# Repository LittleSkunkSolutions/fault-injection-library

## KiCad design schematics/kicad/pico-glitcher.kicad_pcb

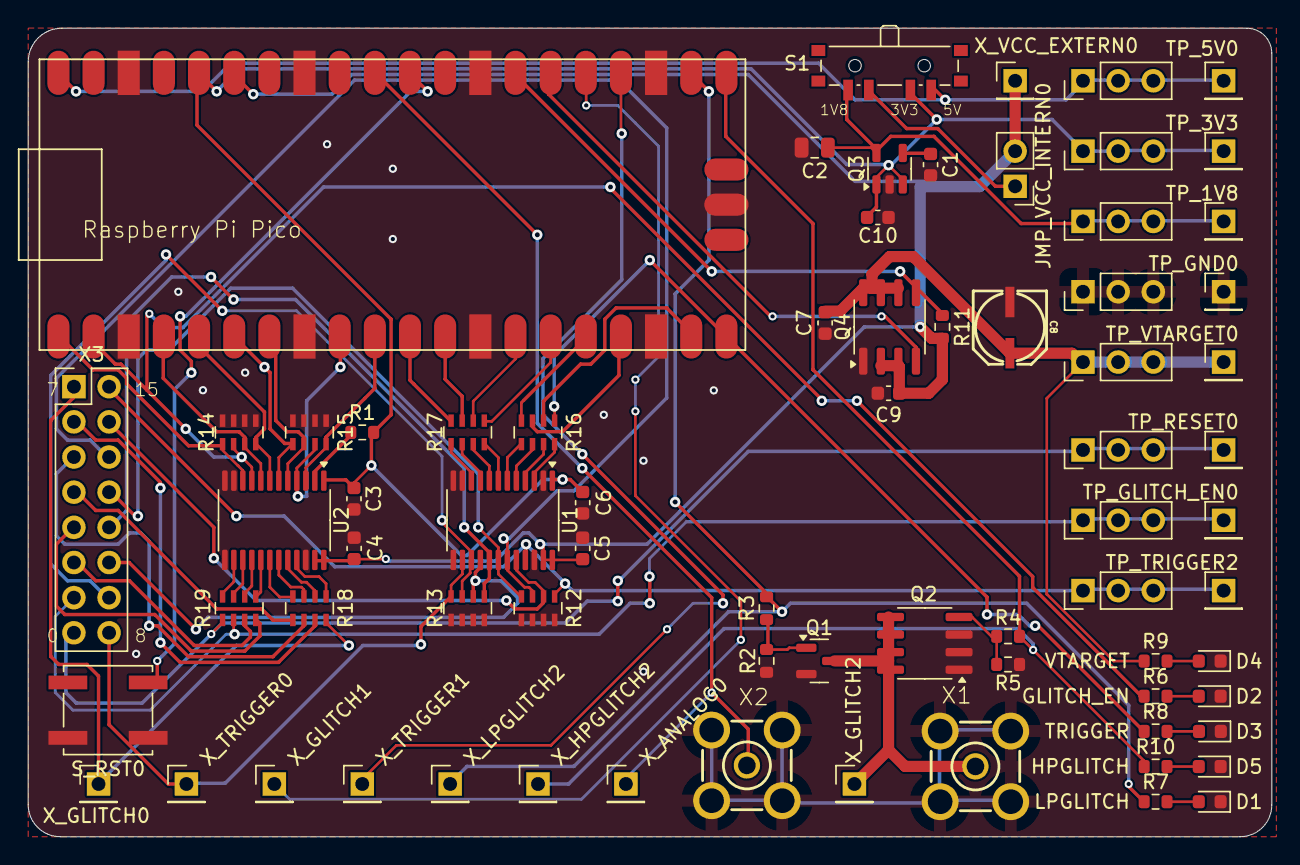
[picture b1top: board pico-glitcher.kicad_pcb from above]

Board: 2 copper layers, 89.8 x 58.4 mm, 72 parts (0 on the bottom side), 73 nets.

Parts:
C1: 10nF; C_0603_1608Metric
C2: 2.2u; C_0805_2012Metric
C3, C4, C5, C6, C7, C9, C10: 0.1uF; C_0603_1608Metric
C8: 22uF; PANASONIC_C
D1: LED_RED_LPGLITCH; LED_0603_1608Metric
D2: LED_BLUE_GLITCH_EN; LED_0603_1608Metric
D3: LED_BLUE_TRIGGER2; LED_0603_1608Metric
D4: LED_RED_TARGET_POWER; LED_0603_1608Metric
D5: LED_RED_HPGLITCH; LED_0603_1608Metric
JMP_VCC_INTERN0: JMP_VCC_INTERN; PinHeader_1x02_P2.54mm_Vertical
PICO0: Raspberry Pi; RPI_PICO
Q1: IRLML2502; SOT-23
Q2: IRF7807PBF; SOIC-8_3.9x4.9mm_P1.27mm
Q3: TPS 79318; SOT-23-5
Q4: TPS2041; SOIC-8_3.9x4.9mm_P1.27mm
R1, R2, R5, R11: 10K; R_0603_1608Metric
R3, R4: 1R; R_0603_1608Metric
R6, R7, R8, R10: 150; R_0603_1608Metric
R9: 220; R_0603_1608Metric
R12, R13, R14, R15: 10k; R_Array_Concave_4x0603
R16, R17, R18, R19: 100; R_Array_Concave_4x0603
S1: Micro Slide Switch; SW_SP3T_PCM13
S_RST0: SW_Push_Shielded; SW_Push_1P1T_NO_CK_KSC7xxJ
TP_1V8, TP_3V3: PINHDR_1X1; PinHeader_1x01_P2.54mm_Vertical
TP_5V0: M01PTH; PinHeader_1x01_P2.54mm_Vertical
TP_GLITCH_EN0: PINHDR_1X1; PinHeader_1x01_P2.54mm_Vertical
TP_GND0: PINHDR_1X1; PinHeader_1x01_P2.54mm_Vertical
TP_RESET0: PINHDR_1X1; PinHeader_1x01_P2.54mm_Vertical
TP_TRIGGER2: PINHDR_1X1; PinHeader_1x01_P2.54mm_Vertical
TP_VTARGET0: PINHDR_1X1; PinHeader_1x01_P2.54mm_Vertical
U1, U2: NH245; TSSOP-24_4.4x7.8mm_P0.65mm
X1, X2: BU-SMA
X3: M08X2; PinHeader_2x08_P2.54mm_Vertical
X_1V8, X_3V3, X_5V0: PINHDR_3X1; PinHeader_1x03_P2.54mm_Vertical
X_ANALOG0: PINHDR_1X1; PinHeader_1x01_P2.54mm_Vertical
X_GLITCH0, X_GLITCH1, X_GLITCH2: PINHDR_1X1; PinHeader_1x01_P2.54mm_Vertical
X_GLITCH_EN0: PINHDR_3X1; PinHeader_1x03_P2.54mm_Vertical
X_GND0: PINHDR_3X1; PinHeader_1x03_P2.54mm_Vertical
X_HPGLITCH2: PINHDR_1X1; PinHeader_1x01_P2.54mm_Vertical
X_LPGLITCH2: PINHDR_1X1; PinHeader_1x01_P2.54mm_Vertical
X_RESET0: PINHDR_3X1; PinHeader_1x03_P2.54mm_Vertical
X_TRIGGER0, X_TRIGGER1: PINHDR_1X1; PinHeader_1x01_P2.54mm_Vertical
X_TRIGGER2: PINHDR_3X1; PinHeader_1x03_P2.54mm_Vertical
X_VCC_EXTERN0: PINHDR_1X1; PinHeader_1x01_P2.54mm_Vertical
X_VTARGET0: PINHDR_3X1; PinHeader_1x03_P2.54mm_Vertical

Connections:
+3V3: C3.1, C6.1, C10.1, PICO0.3V3, Q3.1 (IN), Q3.3 (/EN), R1.2, S1.2, TP_3V3.1, U1.1 (VCCA), U2.1 (VCCA), X_3V3.1, X_3V3.2, X_3V3.3
+5V: PICO0.VBUS, S1.1, TP_5V0.1, X_5V0.1, X_5V0.2, X_5V0.3
/+1V8: C2.1, Q3.5 (OUT), S1.4, TP_1V8.1, X_1V8.1, X_1V8.2, X_1V8.3
/ANALOG: PICO0.GP26_A0, X2.1, X_ANALOG0.1
/GP0: PICO0.GP0, R14.5, U2.10 (A8)
/GP1: PICO0.GP1, R6.1, R14.6, U2.9 (A7)
/GP2: PICO0.GP2, R14.7, U2.8 (A6)
/GP3: PICO0.GP3, R14.8, U2.7 (A5)
/GP4: PICO0.GP4, R15.5, U2.6 (A4)
/GP5: PICO0.GP5, R15.6, U2.5 (A3)
/GP6: PICO0.GP6, R15.7, U2.4 (A2)
/GP7: PICO0.GP7, R15.8, U2.3 (A1)
/GP8: PICO0.GP8, R17.4
/GP9: PICO0.GP9, R17.3
/GP10: PICO0.GP10, R17.2
/GP11: PICO0.GP11, R17.1
/GP12: PICO0.GP12, R16.4
/GP13: PICO0.GP13, R16.3
/GP14: PICO0.GP14, R16.2
/GP15: PICO0.GP15, R8.1, R16.1
/HPGLITCH2: PICO0.GP16, R4.1, R10.1, X_HPGLITCH2.1
/JVCC: JMP_VCC_INTERN0.1, S1.3
/LPGLITCH2: PICO0.GP17, R3.2, R7.1, X_LPGLITCH2.1
/VTARGET: C7.1, C8.1, Q4.6 (OUT), Q4.7 (OUT), Q4.8 (OUT), R9.1, TP_VTARGET0.1, X_VTARGET0.1, X_VTARGET0.2, X_VTARGET0.3
/VTARGET_EN: PICO0.GP20, Q4.4 (/EN)
/VTARGET_OC: PICO0.GP21, Q4.5 (/OC), R11.1
GND: C1.2, C2.2, C3.2, C4.1, C5.1, C6.2, C7.2, C8.2, C9.1, C10.2, D1.1 (K), D2.1 (K), D3.1 (K), D4.1 (K), D5.1 (K), PICO0.AGND, PICO0.GND@1 (GND), PICO0.GND@2 (GND), PICO0.GND@3 (GND), PICO0.GND@4 (GND), PICO0.GND@5 (GND), PICO0.GND@6 (GND), PICO0.GND@7 (GND), PICO0.GND@8 (GND), Q1.2 (S), Q2.1 (S@1), Q2.2 (S@2), Q2.3 (S@3), Q3.2 (GND), Q4.1 (GND), R2.2, R5.1, R12.5, R12.6, R12.7, R12.8, R13.5, R13.6, R13.7, R13.8, R14.1, R14.2, R14.3, R14.4, R15.1, R15.2, R15.3, R15.4, S_RST0.2, TP_GND0.1, U1.2 (DIR), U1.11 (GND), U1.12 (GND), U1.13 (GND), U1.22 (/OE), U2.11 (GND), U2.12 (GND), U2.13 (GND), U2.22 (/OE), X1.2, X1.3 (2), X1.4 (2), X1.5 (2), X2.2, X2.3 (2), X2.4 (2), X2.5 (2), X_GND0.1, X_GND0.2, X_GND0.3
unnamed: D1.2 (A), R7.2
unnamed: D2.2 (A), R6.2
unnamed: D3.2 (A), R8.2
unnamed: D4.2 (A), R9.2
unnamed: D5.2 (A), R10.2
unnamed: PICO0.RUN, S_RST0.1
unnamed: Q1.3 (D), Q2.5 (D@4), Q2.6 (D@3), Q2.7 (D@2), Q2.8 (D@1), X1.1, X_GLITCH2.1
unnamed: Q1.1 (G), R2.1, R3.1
unnamed: Q2.4 (G), R4.2, R5.2
unnamed: C1.1, Q3.4 (NC/FB)
unnamed: R19.6, TP_GLITCH_EN0.1, X3.13, X_GLITCH_EN0.1, X_GLITCH_EN0.2, X_GLITCH_EN0.3
unnamed: R19.5, TP_RESET0.1, X3.15, X_RESET0.1, X_RESET0.2, X_RESET0.3
unnamed: R12.1, TP_TRIGGER2.1, U1.21 (B1), X3.2, X_TRIGGER2.1, X_TRIGGER2.2, X_TRIGGER2.3
unnamed: R16.8, U1.3 (A1)
unnamed: R16.7, U1.4 (A2)
unnamed: R16.6, U1.5 (A3)
unnamed: R16.5, U1.6 (A4)
unnamed: R17.8, U1.7 (A5)
unnamed: R17.7, U1.8 (A6)
unnamed: R17.6, U1.9 (A7)
unnamed: R17.5, U1.10 (A8)
unnamed: R12.2, U1.20 (B2), X3.4
unnamed: R12.3, U1.19 (B3), X3.6
unnamed: R12.4, U1.18 (B4), X3.8
unnamed: R13.1, U1.17 (B5), X3.10
unnamed: R13.2, U1.16 (B6), X3.12
unnamed: R13.3, U1.15 (B7), X3.14
unnamed: R13.4, U1.14 (B8), X3.16, X_TRIGGER0.1
unnamed: R18.1, U2.21 (B1)
unnamed: R18.2, U2.20 (B2)
unnamed: R18.3, U2.19 (B3)
unnamed: R18.4, U2.18 (B4)
unnamed: R19.1, U2.17 (B5)
unnamed: R19.2, U2.16 (B6)
unnamed: R19.3, U2.15 (B7)
unnamed: R19.4, U2.14 (B8)
unnamed: R1.1, U2.2 (DIR)
unnamed: R18.8, X3.1, X_GLITCH0.1
unnamed: R18.7, X3.3
unnamed: R18.6, X3.5
unnamed: R18.5, X3.7
unnamed: R19.8, X3.9
unnamed: R19.7, X3.11
unnamed: PICO0.GP19, X_GLITCH1.1
unnamed: PICO0.GP18, X_TRIGGER1.1
VCC: C4.2, C5.2, C9.2, JMP_VCC_INTERN0.2, PICO0.ADC_VREF, Q4.2 (IN), Q4.3 (IN), R11.2, U1.23 (VCCB), U1.24 (VCCB), U2.23 (VCCB), U2.24 (VCCB), X_VCC_EXTERN0.1

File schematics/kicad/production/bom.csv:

Designator,Footprint,Quantity,Value,LCSC Part #
C1,0603,1,10nF,C307346
"C10, C3, C4, C5, C6, C7, C9",0603,7,0.1uF,C105907
C2,0805,1,2.2u,C77081
C8,PANASONIC_C,1,22uF,C178580
D1,0603,1,LED_RED_LPGLITCH,C19171390
D2,0603,1,LED_BLUE_GLITCH_EN,C5179639
D3,0603,1,LED_BLUE_TRIGGER2,C5179639
D4,0603,1,LED_RED_TARGET_POWER,C19171390
D5,0603,1,LED_RED_HPGLITCH,C19171390
JMP_VCC_INTERN0,PinHeader_1x02_P2.54mm_Vertical,1,JMP_VCC_INTERN,C7501260
Q1,SOT-23,1,IRLML2502,C5364308
Q2,SOIC-8_3.9x4.9mm_P1.27mm,1,IRF7807PBF,C5350865
Q3,SOT-23-5,1,TPS 79318,C7102
Q4,SOIC-8_3.9x4.9mm_P1.27mm,1,TPS2041,C431481
"R1, R11, R2, R5",0603,4,10K,C103199
"R10, R6, R7, R8",0603,4,150,C3016246
"R12, R13, R14, R15",R_Array_Concave_4x0603,4,10k,C396839
"R16, R17, R18, R19",R_Array_Concave_4x0603,4,100,C396838
"R3, R4",0603,2,1R,C140111
R9,0603,1,220,C138284
S1,SW_SP3T_PCM13,1,Micro Slide Switch,C160878
S_RST0,SW_Push_1P1T_NO_CK_KSC7xxJ,1,SW_Push_Shielded,C2845324
"TP_1V8, TP_3V3, TP_GLITCH_EN0, TP_GND0, TP_RESET0, TP_TRIGGER2, TP_VTARGET0, X_ANALOG0, X_GLITCH0, X_GLITCH1, X_GLITCH2, X_HPGLITCH2, X_LPGLITCH2, X_TRIGGER0, X_TRIGGER1, X_VCC_EXTERN0",PinHeader_1x01_P2.54mm_Vertical,16,PINHDR_1X1,C5277086
TP_5V0,PinHeader_1x01_P2.54mm_Vertical,1,M01PTH,C5277086
"U1, U2",TSSOP-24_4.4x7.8mm_P0.65mm,2,NH245,C27643
"X1, X2",BU-SMA,2,BU-SMA,C914559
X3,PinHeader_2x08_P2.54mm_Vertical,1,M08X2,C68234
"X_1V8, X_3V3, X_5V0, X_GLITCH_EN0, X_GND0, X_RESET0, X_TRIGGER2, X_VTARGET0",PinHeader_1x03_P2.54mm_Vertical,8,PINHDR_3X1,C7501261

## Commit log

2024-11-09 Playing around.
